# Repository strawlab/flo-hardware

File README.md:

# Fast-Lock-On (FLO) hardware

**ℹ️ The main FLO repository is at https://github.com/strawlab/flo ℹ️**.

This repository hosts build instructions and manual for the FLO Bring Your Own
(BYO) camera insect tracking/filming. Included are hardware design files and other large,
binary files.

FLO is a method for videography using a camera system that automatically moves
to follow the subject.

FLO is described in the following publication:

[FLO paper]: https://doi.org/10.1101/2023.12.20.572558

Vo-Doan TT, Titov VV, Harrap MJM, Lochner S, Straw AD. High Resolution Outdoor Videography of Insects Using Fast Lock-On Tracking. bioRxiv (2023) [doi:10.1101/2023.12.20.572558][FLO paper].

## What is in this repository

### Mini-FLO

A bare-minimum hardware

### BYO-camera setup

"Bring Your Own Camera".

The setup for filming flying bees carrying a retroreflective marker.

[hardware description is in ./byo directory](./byo/readme.md)

.jpg>)

## Other links

- https://github.com/strawlab/red-button-trigger-timestamp hardware to record
  times of external trigger events.

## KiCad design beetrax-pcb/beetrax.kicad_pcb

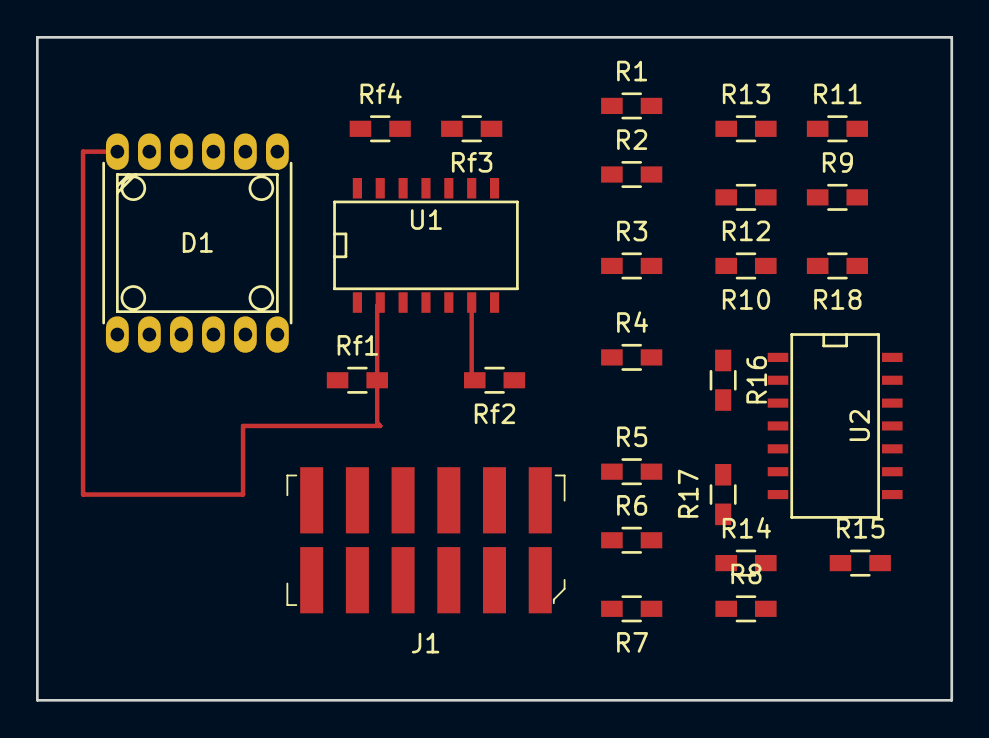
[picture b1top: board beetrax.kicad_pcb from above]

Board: 2 copper layers, 50.8 x 36.8 mm, 26 parts (0 on the bottom side), 22 nets.

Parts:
D1: OPR5911; eDIP-12
J1: 0015912120; PinHeader_2x6_P2.54mm_Vertical_SMD
R1, R2, R3, R4, R5, R6, R7, R8, R9, R10, R11, R12, R13, R14, R15, R16, R17, R18: R; R_0603_HandSoldering
Rf1, Rf2, Rf3, Rf4: R; R_0603_HandSoldering
U1, U2: LT1885; SOIC-14_N

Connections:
GND: J1.5, R13.1, R14.1, R15.1, U1.3, U1.10
unnamed: D1.1, Rf1.1, U1.2
unnamed: D1.6, Rf2.2, U1.6
unnamed: D1.7, Rf3.2, U1.9
unnamed: D1.12, Rf4.1, U1.13
unnamed: J1.1, R3.2, R8.2, R9.2, Rf1.2, U1.1
unnamed: J1.2, R16.1, Rf4.2, U1.14, U2.1
unnamed: R4.2, R5.2, R10.2
unnamed: J1.4, R17.1, U2.7
unnamed: R1.2, R6.2, R11.2
unnamed: J1.6, R18.1, U2.8
unnamed: R2.2, R7.2, R12.2
unnamed: J1.11, Rf2.1, U1.7
unnamed: J1.12, Rf3.1, U1.8
unnamed: R1.1, R2.1, R13.2, U2.3
unnamed: R9.1, R10.1, R11.1, R12.1, R18.2, U2.9
unnamed: R5.1, R6.1, R14.2, U2.5
unnamed: R15.2, U2.10
unnamed: R3.1, R4.1, R16.2, U2.2
unnamed: R7.1, R8.1, R17.2, U2.6
VCC: J1.7, U1.4, U2.4
VSS: J1.3, U1.11, U2.11

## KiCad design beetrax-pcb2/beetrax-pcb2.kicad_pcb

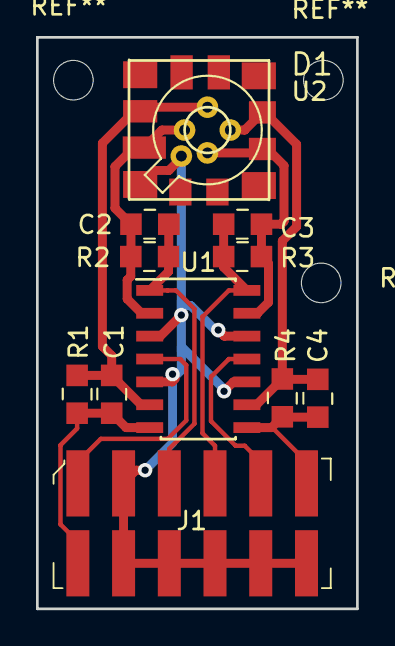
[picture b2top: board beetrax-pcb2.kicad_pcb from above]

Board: 2 copper layers, 17.8 x 31.8 mm, 12 parts (0 on the bottom side), 11 nets.

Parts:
C1, C2, C3, C4: C; 0805
D1: OPR5911
J1: 0015912120; PinHeader_2x6_P2.54mm_Vertical_SMD
R1, R2, R3, R4: R; 0805
U1: LT1885; SOIC-14_3.9x8.7mm_P1.27mm
U2: QP1-6TO; QP1-6TOv2

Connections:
GND: D1.2, J1.2, J1.8, J1.9, J1.10, J1.11, J1.12, U1.3, U1.5, U1.10, U1.12, U2.5
unnamed: C1.1, D1.12, R1.1, U1.6, U2.2
unnamed: C1.2, J1.7, R1.2, U1.7
unnamed: C2.1, D1.1, R2.1, U1.2, U2.1
unnamed: C2.2, J1.3, R2.2, U1.1
unnamed: C3.1, J1.4, R3.1, U1.14
unnamed: C3.2, D1.6, R3.2, U1.13, U2.4
unnamed: C4.1, J1.6, R4.1, U1.8
unnamed: C4.2, D1.7, R4.2, U1.9, U2.3
VCC: J1.1, U1.4
VSS: J1.5, U1.11

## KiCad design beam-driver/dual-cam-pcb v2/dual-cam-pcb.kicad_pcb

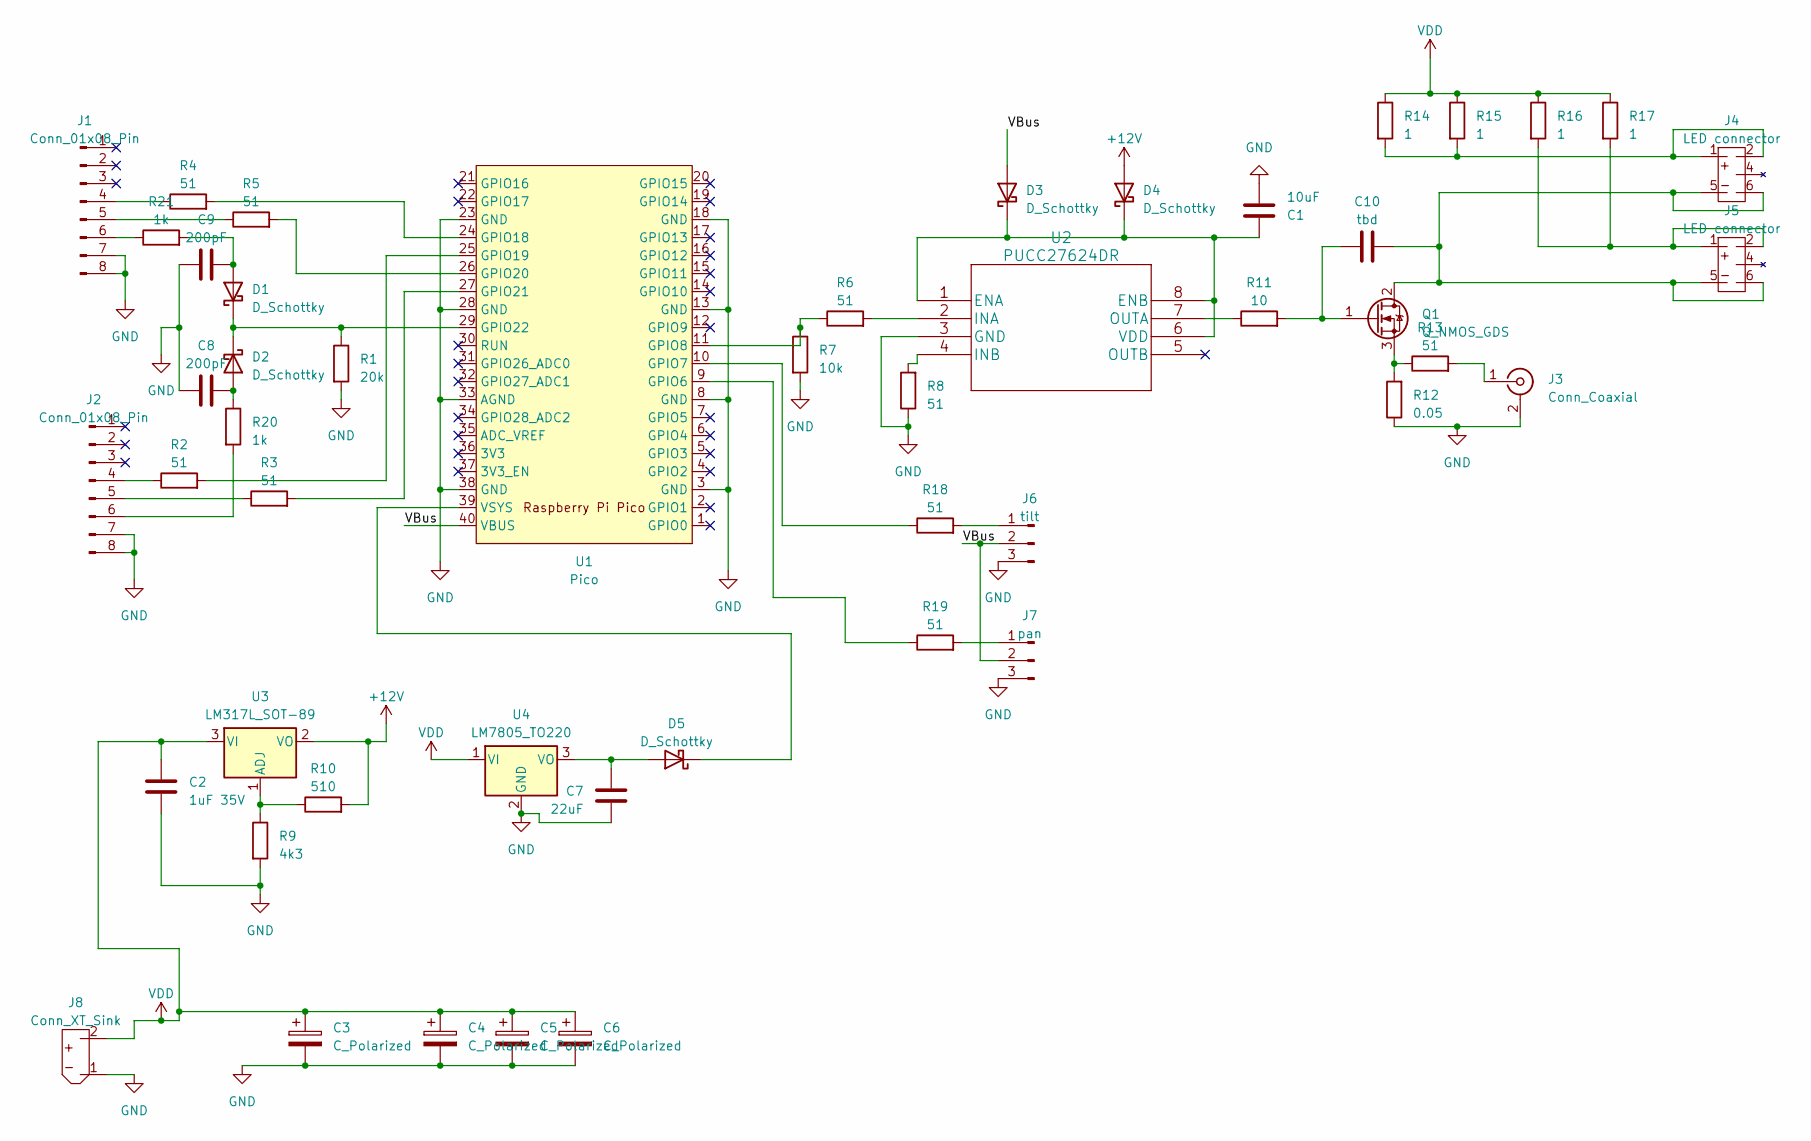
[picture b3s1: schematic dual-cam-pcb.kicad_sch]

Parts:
C1: 10uF; C_0805_2012Metric_Pad1.18x1.45mm_HandSolder
C2: 1uF 35V; C_0805_2012Metric_Pad1.18x1.45mm_HandSolder
C3: C_Polarized; CP_Radial_D18.0mm_P7.50mm
C4, C5, C6: C_Polarized
C7: 22uF; C_1206_3216Metric_Pad1.33x1.80mm_HandSolder
C8, C9: 200pF; C_0603_1608Metric_Pad1.08x0.95mm_HandSolder
C10: tbd; C_0603_1608Metric_Pad1.08x0.95mm_HandSolder
D1, D2: D_Schottky; D_MicroMELF_Handsoldering
D3, D4, D5: D_Schottky; D_0805_2012Metric_Pad1.15x1.40mm_HandSolder
J1, J2: Conn_01x08_Pin; PinHeader_1x08_P2.54mm_Vertical
J3: Conn_Coaxial; SMA_Amphenol_901-144_Vertical
J4, J5: LED connector; Conn_LED_source
J6: tilt; PinHeader_1x03_P2.54mm_Vertical
J7: pan; PinHeader_1x03_P2.54mm_Vertical
J8: Conn_XT_Sink; AMASS_XT30U-M_1x02_P5.0mm_Vertical
Q1: Q_NMOS_GDS; TO-252-2
R1: 20k; R_0603_1608Metric_Pad0.98x0.95mm_HandSolder
R2, R3, R4, R5, R6, R8, R13, R18, R19: 51; R_0603_1608Metric_Pad0.98x0.95mm_HandSolder
R7: 10k; R_0603_1608Metric_Pad0.98x0.95mm_HandSolder
R9: 4k3; R_0603_1608Metric_Pad0.98x0.95mm_HandSolder
R10: 510; R_0603_1608Metric_Pad0.98x0.95mm_HandSolder
R11: 10; R_0603_1608Metric_Pad0.98x0.95mm_HandSolder
R12: 0.05; R_2010_5025Metric_Pad1.40x2.65mm_HandSolder
R14, R15, R16, R17: 1; R_Axial_DIN0411_L9.9mm_D3.6mm_P5.08mm_Vertical
R20, R21: 1k; R_0603_1608Metric_Pad0.98x0.95mm_HandSolder
U1: Pico; RPi_Pico_SMD
U2: PUCC27624DR; SOIC-8_3.9x4.9mm_P1.27mm
U3: LM317L_SOT-89; SOT-89-3
U4: LM7805_TO220; TO-220-3_Vertical

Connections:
+12V: D4.2 (A), R10.2, U3.2 (VO)
/VBus: D3.2 (A), J6.2, J7.2, U1.40 (VBUS)
GND: C1.2, C2.2, C3.2, C4.2, C5.2, C6.2, C7.1, C8.2, C9.2, J1.7, J1.8, J2.7, J2.8, J3.2 (Ext), J6.3, J7.3, J8.1 (minus1), R1.2, R7.2, R8.1, R9.2, R12.1, U1.3 (GND), U1.8 (GND), U1.13 (GND), U1.18 (GND), U1.23 (GND), U1.28 (GND), U1.33 (AGND), U1.38 (GND), U2.3 (GND), U4.2 (GND)
unnamed: C9.1, D1.2 (A), R21.2
unnamed: D1.1 (K), D2.1 (K), R1.1, U1.29 (GPIO22)
unnamed: C8.1, D2.2 (A), R20.1
unnamed: C1.1, D3.1 (K), D4.1 (K), U2.1 (ENA), U2.6 (VDD), U2.8 (ENB)
unnamed: C7.2, D5.2 (A), U4.3 (VO)
unnamed: D5.1 (K), U1.39 (VSYS)
unnamed: J1.4, R4.1
unnamed: J1.5, R5.1
unnamed: J1.6, R21.1
unnamed: J2.4, R2.1
unnamed: J2.5, R3.1
unnamed: J2.6, R20.2
unnamed: J3.1 (In), R13.2
unnamed: C10.1, J4.5 (minus1), J4.6 (minus2), J5.5 (minus1), J5.6 (minus2), Q1.2 (D)
unnamed: J4.1 (plus1), J4.2 (plus2), R14.2, R15.2
unnamed: J5.1 (plus1), J5.2 (plus2), R16.2, R17.2
unnamed: J6.1, R18.2
unnamed: J7.1, R19.2
unnamed: C10.2, Q1.1 (G), R11.2
unnamed: Q1.3 (S), R12.2, R13.1
unnamed: R19.1, U1.9 (GPIO6)
unnamed: R18.1, U1.10 (GPIO7)
unnamed: R6.1, R7.1, U1.11 (GPIO8)
unnamed: R4.2, U1.24 (GPIO18)
unnamed: R2.2, U1.25 (GPIO19)
unnamed: R5.2, U1.26 (GPIO20)
unnamed: R3.2, U1.27 (GPIO21)
unnamed: R6.2, U2.2 (INA)
unnamed: R8.2, U2.4 (INB)
unnamed: R11.1, U2.7 (OUTA)
unnamed: R9.1, R10.1, U3.1 (ADJ)
VDD: C2.1, C3.1, C4.1, C5.1, C6.1, J8.2 (plus), R14.1, R15.1, R16.1, R17.1, U3.3 (VI), U4.1 (VI)

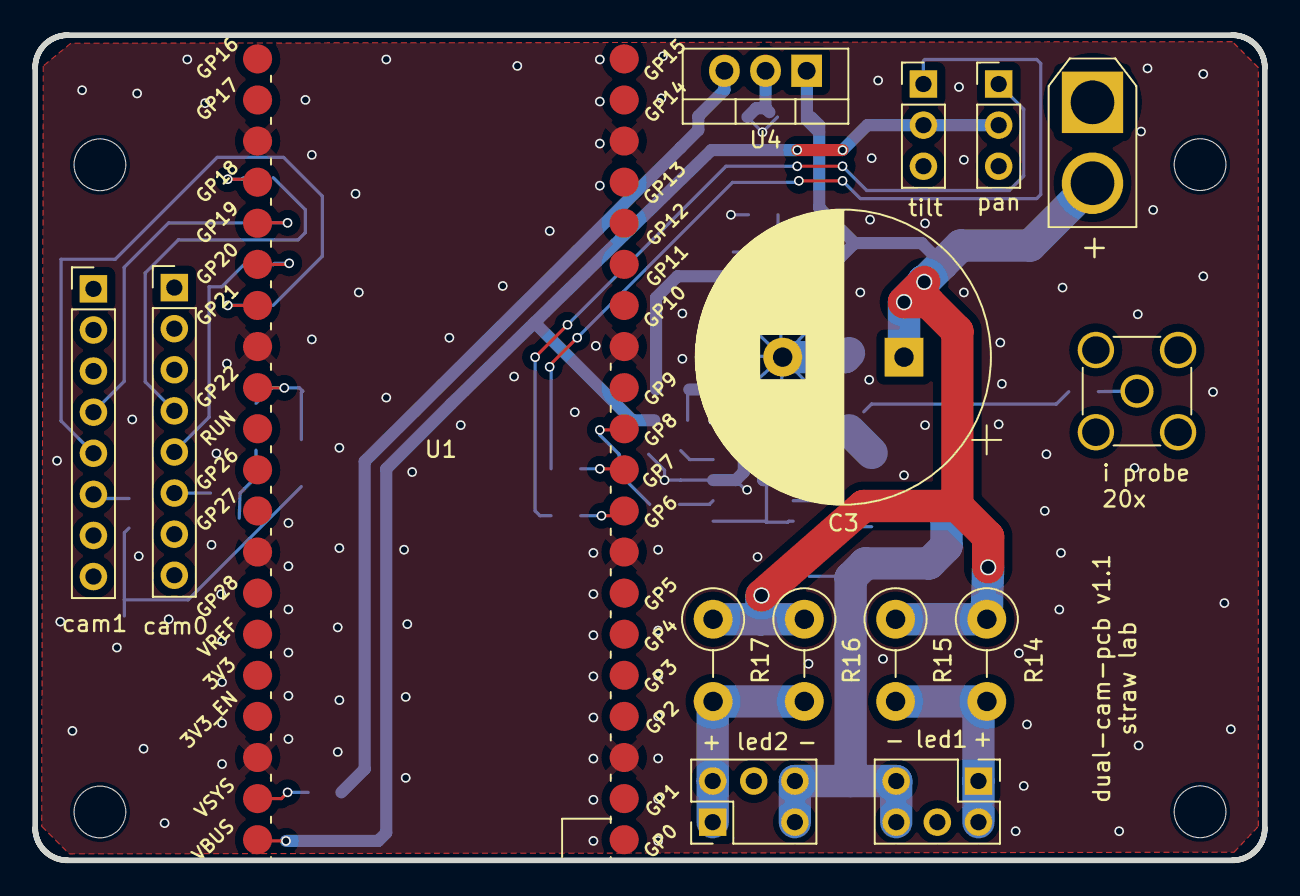
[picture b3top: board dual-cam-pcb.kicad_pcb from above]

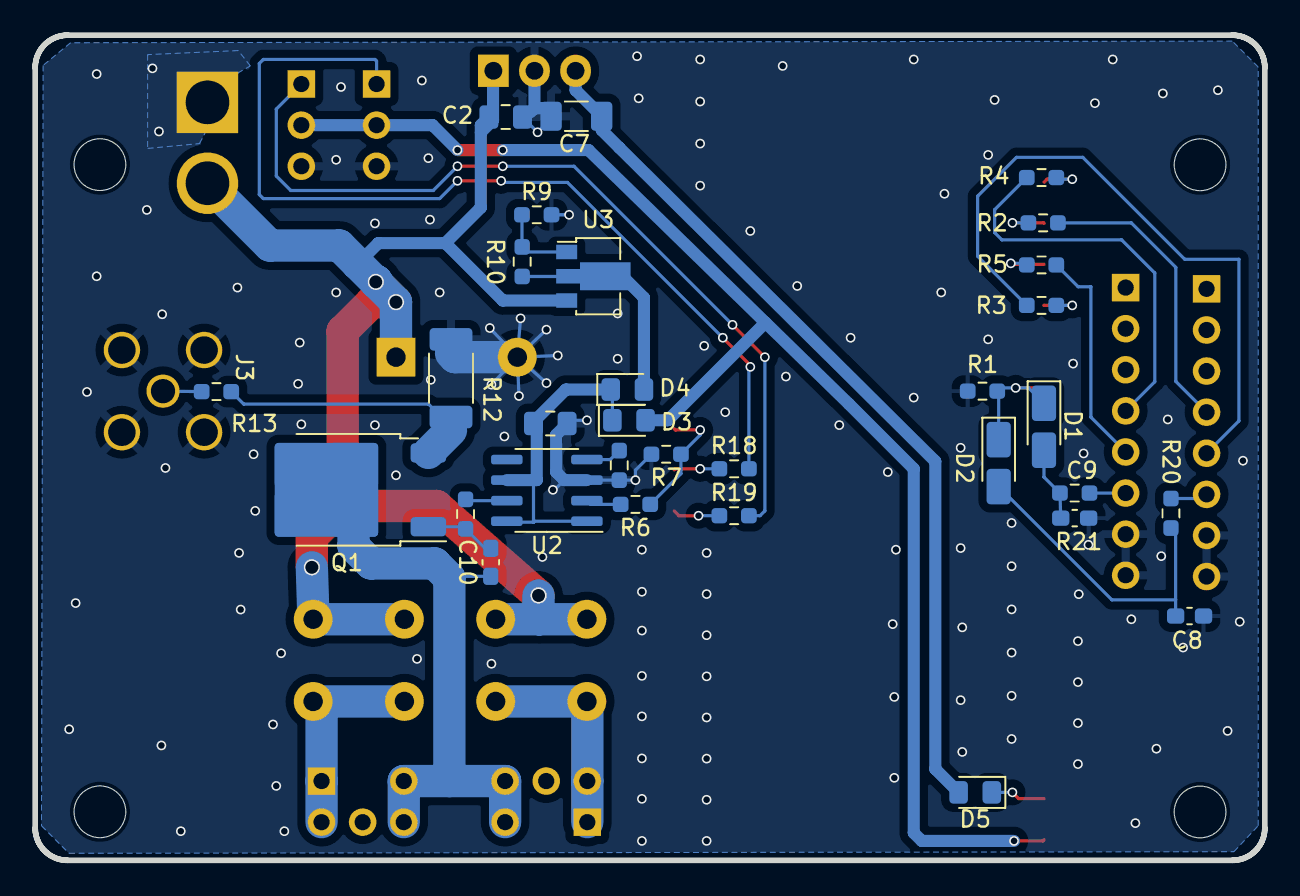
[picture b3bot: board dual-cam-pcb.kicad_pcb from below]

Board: 2 copper layers, 76.0 x 51.0 mm, 46 parts (31 on the bottom side), 35 nets.

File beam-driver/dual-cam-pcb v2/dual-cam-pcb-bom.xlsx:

Id | Designator | Footprint | Quantity | Designation | Supplier and ref | brand | comment
23 | C1 | C_0805_2012Metric_Pad1.18x1.45mm_HandSolder | 1 | MLCC 10uF 16V, size 0805 |  |  | bypass cap, value is not critical
26 | C2 | C_0805_2012Metric_Pad1.18x1.45mm_HandSolder | 1 | MLCC 1uF 35V, size 0805 |  |  | bypass cap, value is not critical
8 | C3 | CP_Radial_D18.0mm_P7.50mm | 1 | Electrolytic capacitor 3300uF 35V |  |  | overkill. 1200uF should be enough.
17 | C7 | C_0805_2012Metric_Pad1.18x1.45mm_HandSolder | 1 | MLCC 22uF 6.5V, size 0805 |  |  | affects stability of 7805, value is important
25 | C8,C9 | C_0603_1608Metric_Pad1.08x0.95mm_HandSolder | 2 | MLCC 200pF 6.5V, size 0603 |  |  | emi filter, value is important
21 | D2,D1 | D_MicroMELF_Handsoldering | 2 | schottky diode (Micro-MELF) | BAS85-GS08 | Vishay
12 | D4,D5,D3 | D_0805_2012Metric_Pad1.15x1.40mm_HandSolder | 3 | schottky diode size 0805 | SD0805S020S1R0 | Kyocera
3 | J2,J1 | PinHeader_1x08_P2.54mm_Vertical | 2 | 0.1 inch pin header straight 1x8
2 | J3 | SMA_Amphenol_901-144_Vertical | 1 | SMA connector through-hole | 471-SMACONNECTOR | LPRS
4 | J4,J5 | Conn_LED_source | 2 | 0.1-inch socket (through-hole) 2x3 |  |  | there is a missing hole on the board as a polarity key. Plug the hole in the so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
9 | J6, J7 | PinHeader_1x03_P2.54mm_Vertical | 2 | 0.1-inch pin header straight 1x3 |  |  | optional (intended for connecting pan-tilt hobby servo motors)
7 | J8 | AMASS_XT30U-M_1x02_P5.0mm_Vertical | 1 | XT-30 connector | XT60U-M | Amass
22 | Q1 | TO-252-2 | 1 | n-channel MOSFET | TK6R7P06PL | Toshiba
24 | R1 | R_0603_1608Metric_Pad0.98x0.95mm_HandSolder | 1 | resistor 20 KOhm, size 0605
19 | R10 | R_0603_1608Metric_Pad0.98x0.95mm_HandSolder | 1 | resistor 510 ohm, size 0605
11 | R11 | R_0603_1608Metric_Pad0.98x0.95mm_HandSolder | 1 | resistor 10 ohms, size 0605
14 | R12 | R_2010_5025Metric_Pad1.40x2.65mm_HandSolder | 1 | resistor 0.05 ohm, size 2010 | LVK12R050DER | Ohmite
1 | R14,R16,R15,R17 | R_Axial_DIN0411_L9.9mm_D3.6mm_P5.08mm_Vertical | 4 | 1 Ohm 1 W through-hole resistor
13 | R19,R6,R2,R3,R8,R13,R5,R18,R4 | R_0603_1608Metric_Pad0.98x0.95mm_HandSolder | 9 | resistor 51 ohms, size 0605
18 | R20,R21 | R_0603_1608Metric_Pad0.98x0.95mm_HandSolder | 2 | resistor 1 KOhm, size 0605
16 | R7 | R_0603_1608Metric_Pad0.98x0.95mm_HandSolder | 1 | resistor 10 KOhm, size 0605
27 | R9 | R_0603_1608Metric_Pad0.98x0.95mm_HandSolder | 1 | resistor 4.3 KOhm, size 0605
5 | U1 | RPi_Pico_SMD | 1 | Raspberry-Pi Pico | Raspberry-Pi Pico | Raspberry-Pi
20 | U2 | SOIC-8_3.9x4.9mm_P1.27mm | 1 | gate driver UCC27624DR | UCC27624DR | Texas Instruments
15 | U3 | SOT-89-3 | 1 | LM317L (SOT-89) | LM317LIPK | Texas Instruments
6 | U4 | TO-220-3_Vertical | 1 | 7805 (TO220) | NJM7805FA | JRC

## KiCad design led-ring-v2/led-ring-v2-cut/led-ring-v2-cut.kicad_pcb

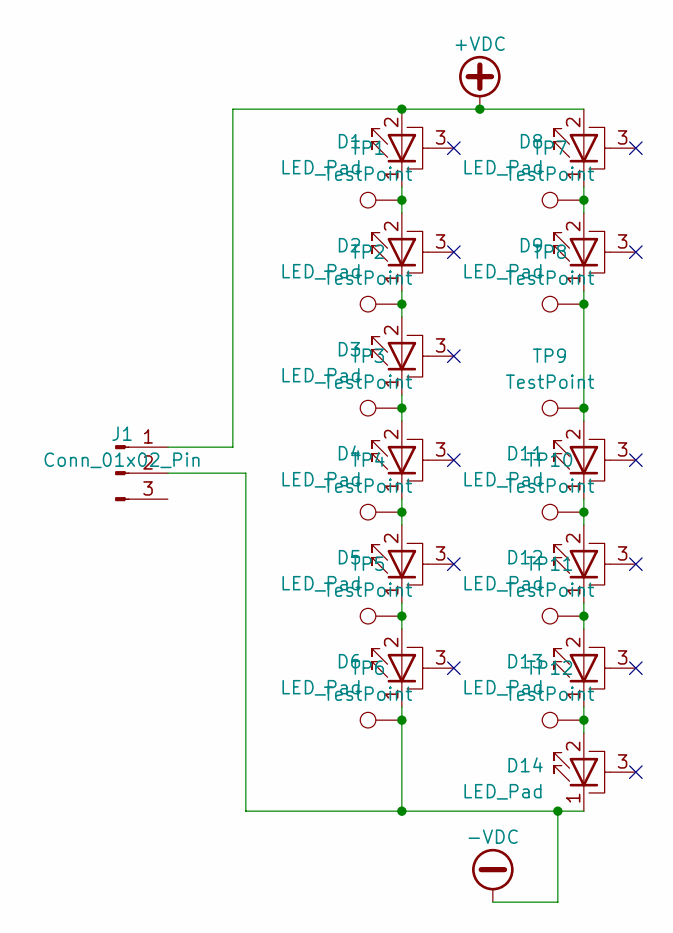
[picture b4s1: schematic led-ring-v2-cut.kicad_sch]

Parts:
D1, D2, D3, D4, D5, D6, D8, D9, D11, D12, D13, D14: LED_Pad; OSRAM_SFH_4715AS_with_LISA4
J1: Conn_01x02_Pin; strawlab_led_conn_M_smd
TP1, TP2, TP3, TP4, TP5, TP6, TP7, TP8, TP9, TP10, TP11, TP12: TestPoint; TestPoint_Pad_D1.0mm_paste

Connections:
+VDC: D1.2 (A), D8.2 (A), J1.1
-VDC: D6.1 (K), D14.1 (K), J1.2, TP6.1
unnamed: D1.1 (K), D2.2 (A), TP1.1
unnamed: D2.1 (K), D3.2 (A), TP2.1
unnamed: D3.1 (K), D4.2 (A), TP3.1
unnamed: D4.1 (K), D5.2 (A), TP4.1
unnamed: D5.1 (K), D6.2 (A), TP5.1
unnamed: D8.1 (K), D9.2 (A), TP7.1
unnamed: D9.1 (K), D11.2 (A), TP8.1, TP9.1
unnamed: D11.1 (K), D12.2 (A), TP10.1
unnamed: D12.1 (K), D13.2 (A), TP11.1
unnamed: D13.1 (K), D14.2 (A), TP12.1

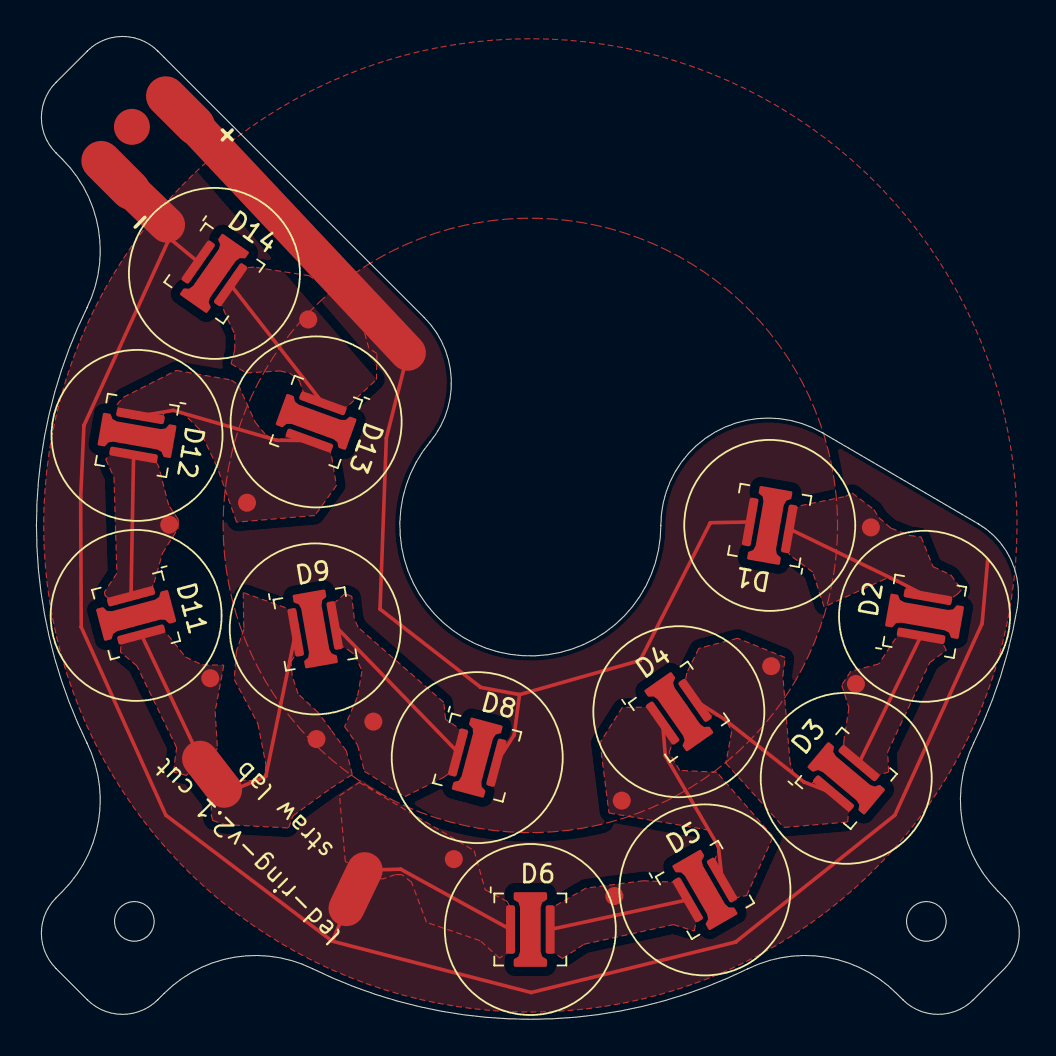
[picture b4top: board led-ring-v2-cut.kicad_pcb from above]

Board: 2 copper layers, 54.6 x 54.6 mm, 25 parts (0 on the bottom side), 12 nets.

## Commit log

2023-10-16 first commit!
    add .gitignore
2023-10-16 add bom, pcbs, some 3d prints
2023-10-17 update beam-driver pcb
    to include emi filter on ExposureActive camera GPIO.
    + update gerbers
2023-10-17 Add led driver components to bom
    + a few other minor changes to bom
2023-10-18 add step files for focusing parts
2023-10-23 move byo stuff into `byo` folder
    in anticipation of adding other flo hardware here
2023-10-23 document trigger cable
2023-10-23 start writing docs
2023-10-26 created mini-pan-tilt subfolder for build instructions
2023-10-26 typo
2023-10-26 added linux screenshots
2023-10-26 forgotten to save
2023-10-26 comments in flo-bui.png
2023-10-26 more pictures and more text
2023-10-26 more text
2023-10-26 drawing on pictures
2023-10-26 note on scope termination in byo/readme
2023-10-27 added instructions to run gimbal version
2023-10-28 fix belt profile name
2023-10-29 add 3d print parts
2023-11-07 make files smaller
2023-11-07 remove gcode
2023-11-07 remove beam driver and trigger cable as SciRob as 25 MB limit
2023-12-14 led-ring-v2.1
    * fix polarity markings
    * add lens circles to aid glue deposition
2023-12-14 create cut version of led ring
2023-12-14 led-ring-v2-cut: fab files
2023-12-15 mention cut pcb in instructions
2023-12-15 update dual-cam-pcb
    * change some footprints
    * add miller capacitor (to smooth out led transitions)
    * add pcb name
    * minor layout changes
2023-12-15 delete outdated gerbers
    fab services accept kicadpcbs directly, usually
2024-01-02 update BYO BOM
    * fix "system" field for pantilt components
    * update led-ring references to cut version
    * add power supplies
    * add usb cables for motors
    * add some part numbers for dual-cam-pcb
    * other changes
2024-01-03 add bugs.txt for dual-cam-pcb
2024-01-06 dual-cam-pcb: update cheatsheet layer
2024-01-12 add some firmware binaries
2024-01-31 tilt mirror motor new version
2024-01-31 fixes to tilt_mirror_rotor
    * fix mirror slot being too wide
    * increase knob spiral pitch
    * reduce bulk
    * scale belt gear for better meshing
    * add flat surfaces to the balloon part
    * change bearing clamps design
2024-02-09 bom: refine ball head
2024-03-07 Increase thickness of pan cover to 2 mm.
    Some printers can not print the previous version.
2024-05-01 Add CAD files for 3D printed mirror box
2024-09-11 import PCB designs
    from internal `flo` repo commit
    726013358700dc3df1ec6a66a7fca4f67ebcc50a
2024-09-11 more readme update
2024-09-11 link to red-button-trigger-timestamp
2024-09-13 add zenodo doi
2024-09-26 beamdriver: update firmware
2024-09-26 update instructions for mini-pan-tilt
2024-10-08 add mini-pan-tile STL files
2024-10-08 add links to mini-flo STL files
2024-10-10 add firmware for 100 fps beam driver
